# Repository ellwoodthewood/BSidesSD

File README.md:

# BSidesSD

Copy contents of python folder to your badge (including lib folder) to program it. Badge will run code.py when it starts up.

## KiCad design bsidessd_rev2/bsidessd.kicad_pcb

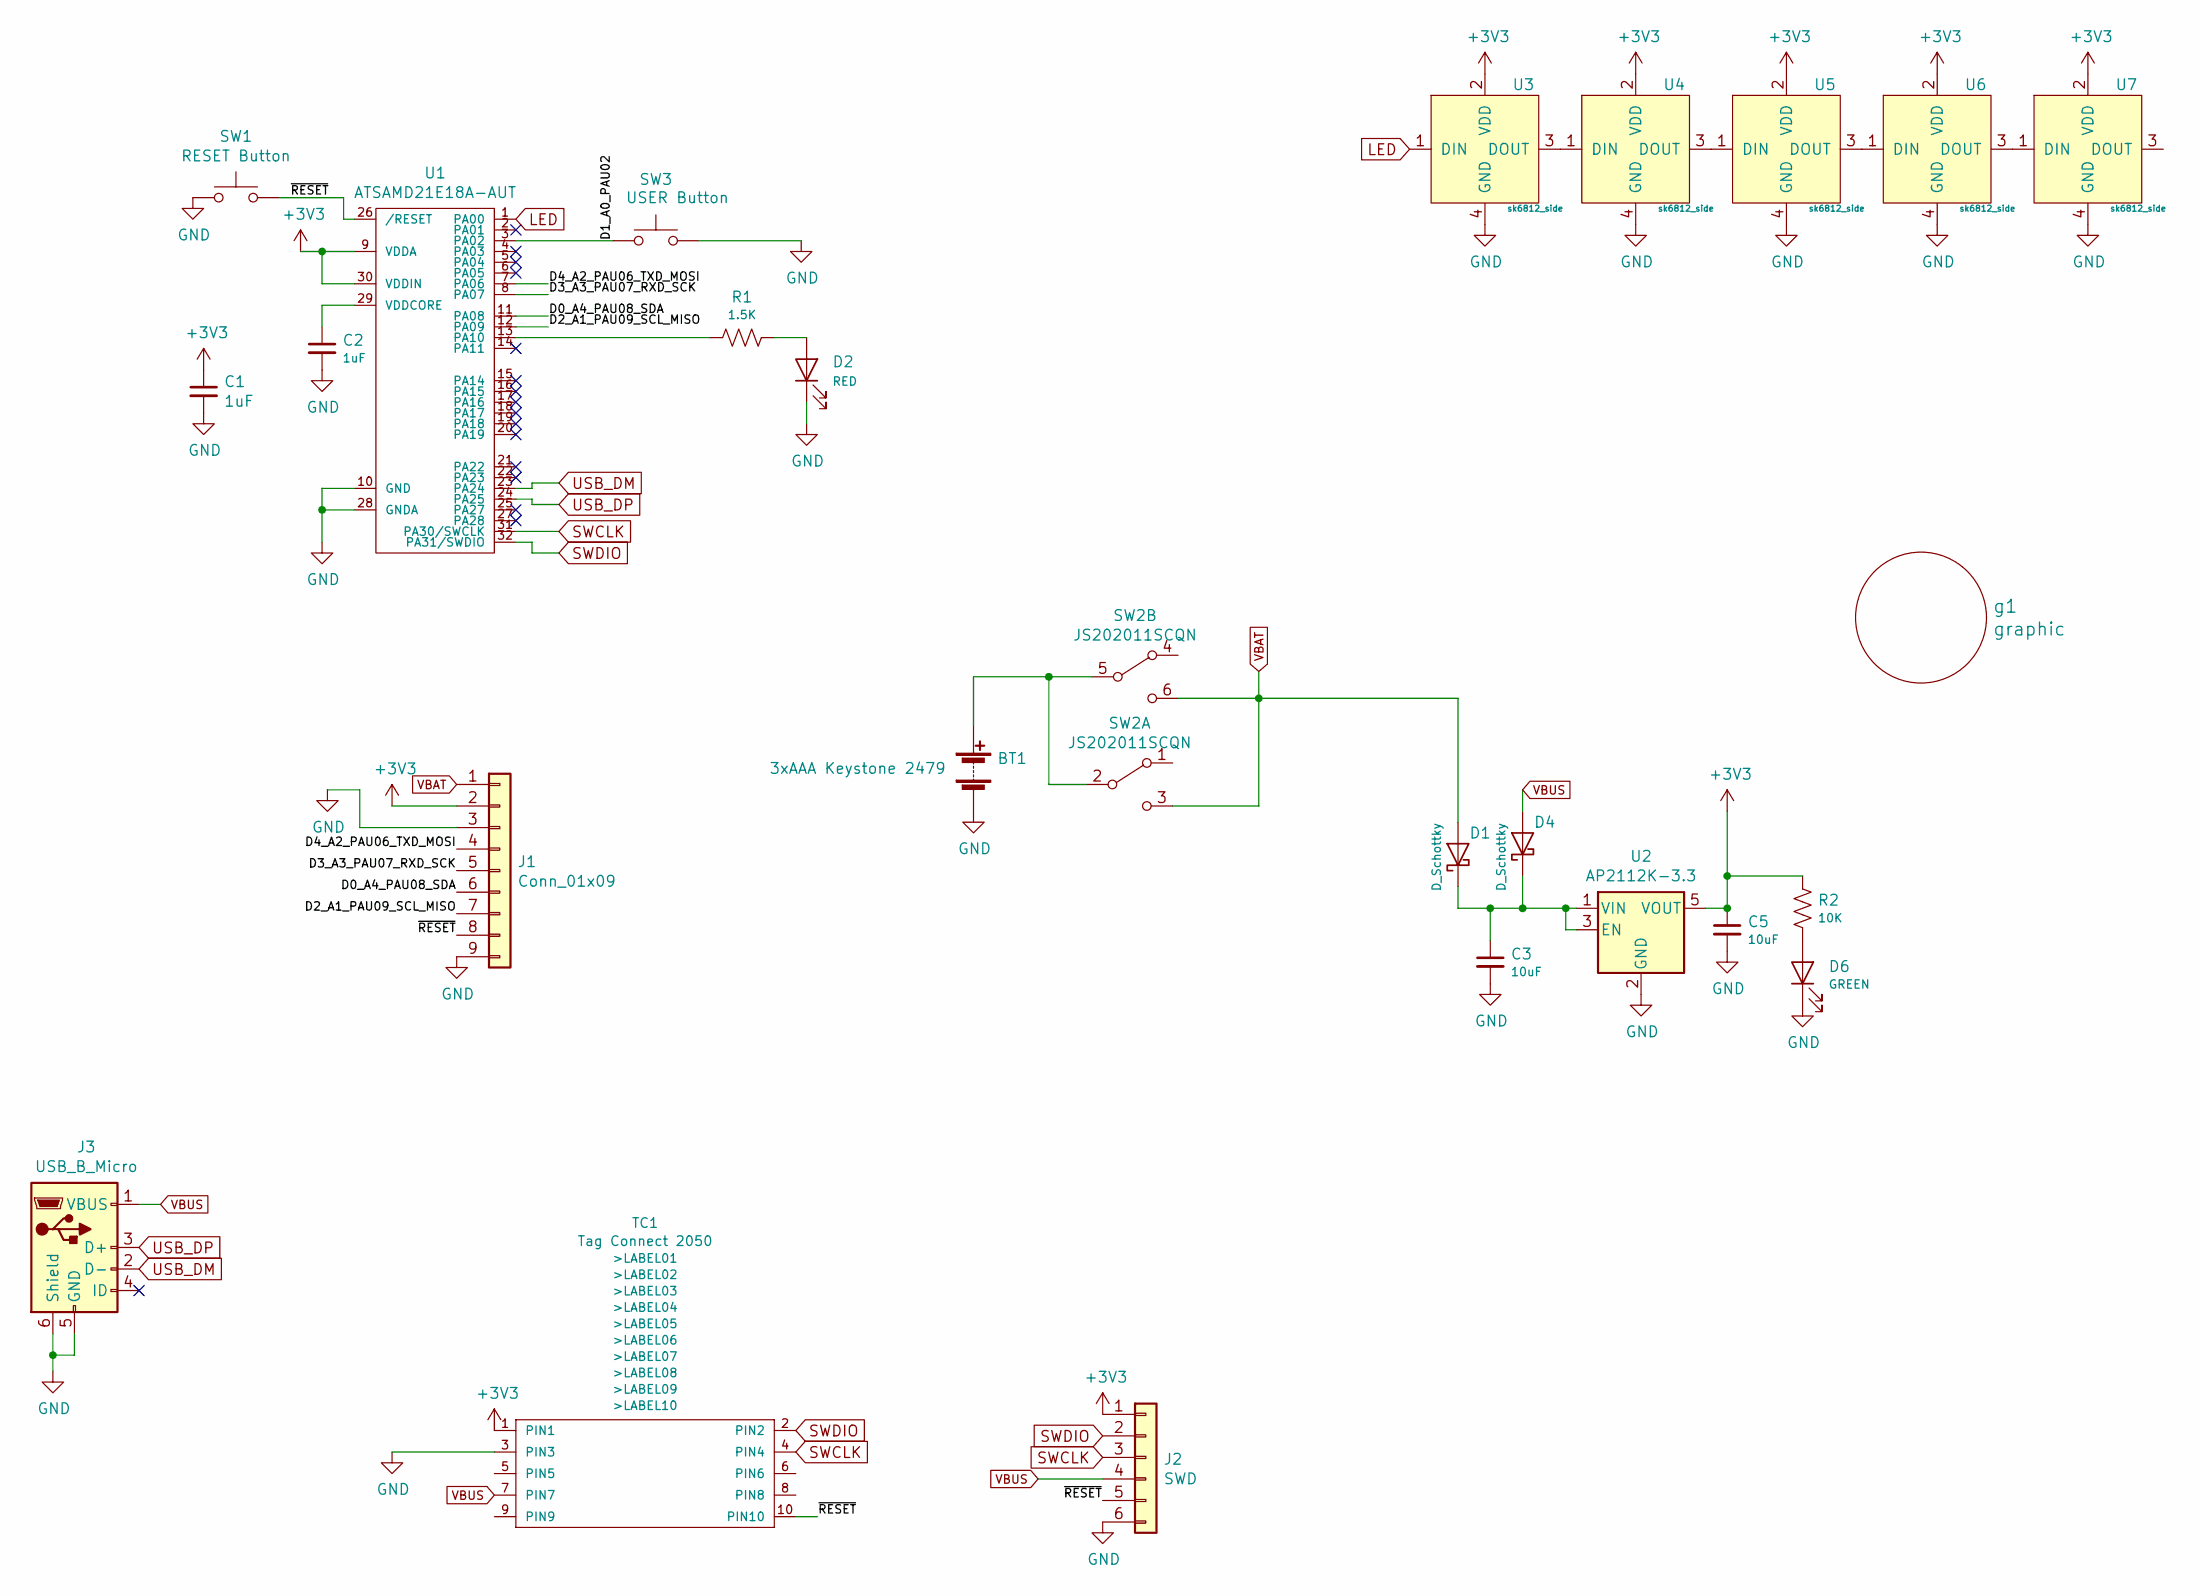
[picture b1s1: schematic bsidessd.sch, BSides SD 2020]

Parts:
BT1: 3xAAA Keystone 2479; BatteryHolder_Keystone_2479_3xAAA
C1, C2: 1uF; C_0805_2012Metric
C3, C5: 10uF; C_0805_2012Metric
D1, D4: D_Schottky; D_SOD-323
D2: RED; LED_0603_1608Metric
D6: GREEN; LED_0603_1608Metric
J1: Conn_01x09; PinHeader_1x09_P2.54mm_Vertical
J2: SWD; PinHeader_1x06_P2.54mm_Vertical
J3: USB_B_Micro; USB_Micro-B_Amphenol_10103594-0001LF_Horizontal
R1: 1.5K; R_0805_2012Metric
R2: 10K; R_0805_2012Metric
SW1: RESET Button; SW_SPST_PTS810
SW2: JS202011SCQN
SW3: USER Button; SW_SPST_PTS810
TC1: Tag Connect 2050; TC2050-IDC-FP-NoSilk
U1: ATSAMD21E18A-AUT; TQFP-32_7x7mm_P0.8mm
U2: AP2112K-3.3; SOT-23-5
U3, U4, U5, U6, U7: sk6812_side; LED_SK6812_SIDE
g1: graphic; bsidessd_rev2

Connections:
+3V3: C1.1, C5.1, J1.2, J2.1, R2.1, TC1.1 (PIN1), U1.9 (VDDA), U1.30 (VDDIN), U2.5 (VOUT), U3.2 (VDD), U4.2 (VDD), U5.2 (VDD), U6.2 (VDD), U7.2 (VDD)
/D0_A4_PAU08_SDA: J1.6, U1.11 (PA08)
/D1_A0_PAU02: SW3.1, U1.3 (PA02); also elsewhere on the board
/D2_A1_PAU09_SCL_MISO: J1.7, U1.12 (PA09)
/D3_A3_PAU07_RXD_SCK: J1.5, U1.8 (PA07)
/D4_A2_PAU06_TXD_MOSI: J1.4, U1.7 (PA06)
/~RESET: J1.8, J2.5, SW1.2, TC1.10 (PIN10), U1.26 (/RESET); also elsewhere on the board
GND: BT1.2 (-), C1.2, C2.2, C3.2, C5.2, D2.1 (K), D6.1 (K), J1.3, J1.9, J2.6, J3.5 (GND), J3.6 (Shield), SW1.1, SW3.2, TC1.3 (PIN3), U1.10 (GND), U1.28 (GNDA), U2.2 (GND), U3.4 (GND), U4.4 (GND), U5.4 (GND), U6.4 (GND), U7.4 (GND); also elsewhere on the board
LED: U1.1 (PA00), U3.1 (DIN)
unnamed: BT1.1 (+), SW2.2 (B), SW2.5 (B)
unnamed: C2.1, U1.29 (VDDCORE)
unnamed: C3.1, D1.1 (K), D4.1 (K), U2.1 (VIN), U2.3 (EN)
unnamed: D2.2 (A), R1.1
unnamed: D6.2 (A), R2.2
unnamed: R1.2, U1.13 (PA10)
unnamed: U3.3 (DOUT), U4.1 (DIN)
unnamed: U4.3 (DOUT), U5.1 (DIN)
unnamed: U5.3 (DOUT), U6.1 (DIN)
unnamed: U6.3 (DOUT), U7.1 (DIN)
SWCLK: J2.3, TC1.4 (PIN4), U1.31 (PA30/SWCLK)
SWDIO: J2.2, TC1.2 (PIN2), U1.32 (PA31/SWDIO)
USB_DM: J3.2 (D-), U1.23 (PA24)
USB_DP: J3.3 (D+), U1.24 (PA25)
VBAT: D1.2 (A), J1.1, SW2.3 (C), SW2.6 (C)
VBUS: D4.2 (A), J2.4, J3.1 (VBUS), TC1.7 (PIN7)

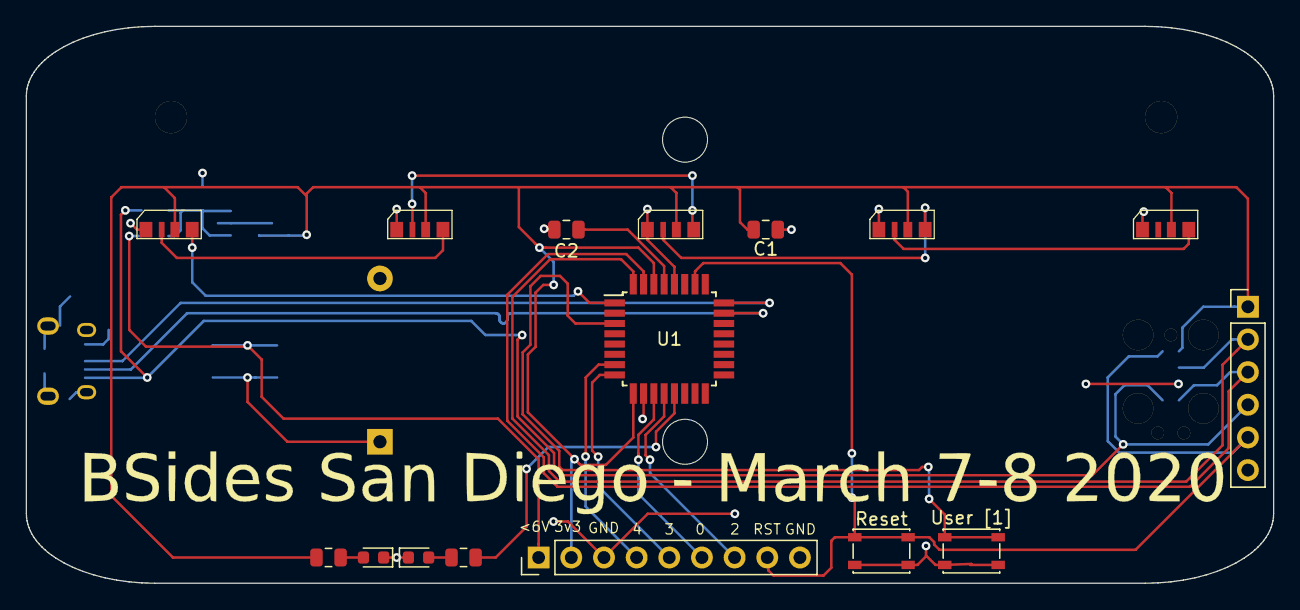
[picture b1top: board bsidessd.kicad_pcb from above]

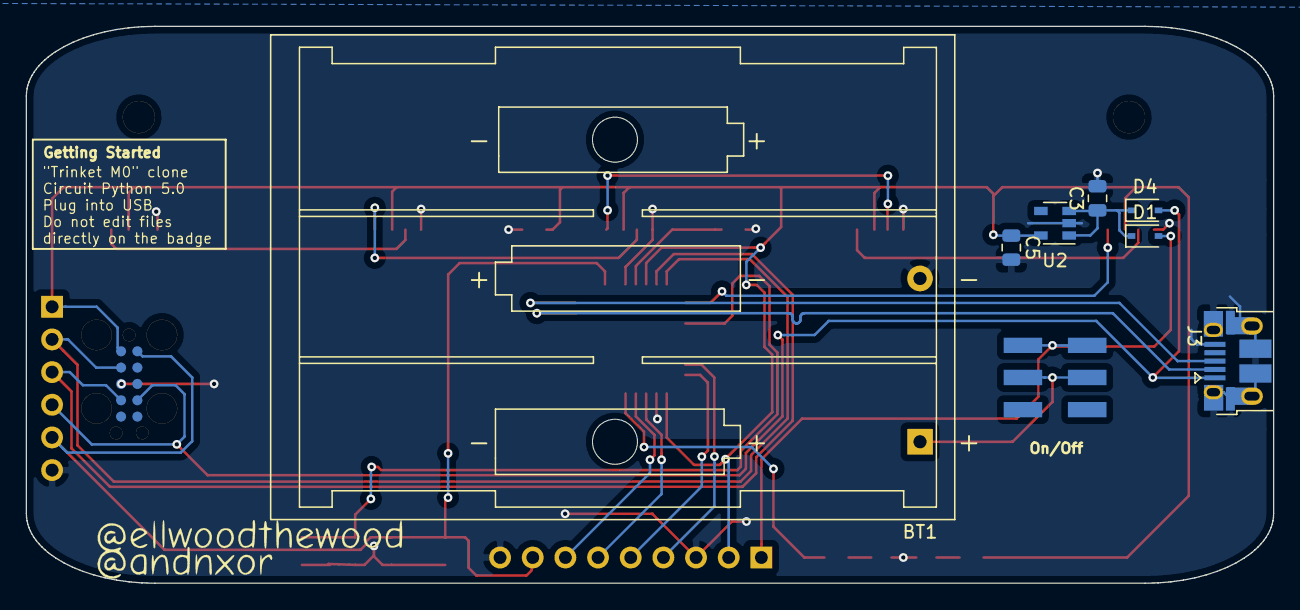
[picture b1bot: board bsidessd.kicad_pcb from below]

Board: 2 copper layers, 97.0 x 43.3 mm, 26 parts (9 on the bottom side), 25 nets.

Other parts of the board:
Reset: RESET Button; SW_SPST_PTS810
User [1]: USER Button; SW_SPST_PTS810

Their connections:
/D1_A0_PAU02: User [1].1; also elsewhere on the board
/~RESET: Reset.2; also elsewhere on the board
GND: Reset.1, User [1].2; also elsewhere on the board

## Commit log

2019-11-26 BSidesSD
    Plans for the upcoming BSidesSD badge. Very much in the works
2019-11-26 update 1
2019-11-26 Initial design started
2019-11-27 Updated samples
2019-11-28 Update to pcb and acrylic
2020-01-01 Logging build of first prototype.
2020-01-01 Initial Circuit Python working.
2020-01-01 Updated with vbatt "crash"
2020-01-02 Found reset and boot issues.
2020-01-02 Starting rev2. Schematic is done. Need a new PCB.
2020-01-03 Passes DRC :) Need a sanity check before ordering.
2020-01-03 Cleaned up traces and silk. Ordered rev2 boards.
2020-01-11 It's alive! HSV to RGB working too.
2020-01-20 Changes to acrylic design
    Modified the design, and called out speakers and sponsors
2020-03-07 l33t mode
2020-03-07 Tons of documentation added :p
2020-03-07 Rainbow mode
2020-03-07 Adding animation and properly abstracted code from @scudzey
2020-03-08 some more badge patterns
2020-03-08 readme
2020-03-08 breaing hbad
2020-03-08 Moving to alt3
2020-03-08 Adding new alt from @scudzey
2020-03-08 Sunset mode
